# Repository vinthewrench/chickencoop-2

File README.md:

# Chicken Coop Controller

**Firmware and host-side tooling for an offline, solar-aware chicken coop controller based on the ATmega32U4.**

This repository contains:
- A **desktop host build** for testing and development
- An **AVR firmware build** for deployment
- A shared `src/` tree with no generated artifacts

The build system is intentionally explicit and boring:
- C++ only
- No generated files in `src/`
- All object files live under `build/`
- Host and firmware builds are independent

Hardware for this repository is frozen at **Chicken Coop Controller V3.0**.
Firmware and host code must conform to the shipped hardware.

---

## Repository Layout

```
├── Makefile
│   # Top-level build orchestrator
│   # Invokes host/ and firmware/ builds
│
├── README.md
│   # Project overview and build instructions
│
├── coop.cfg
│   # Example/default runtime configuration for host testing
│
├── firmware/
│   # AVR firmware for Chicken Coop Controller V3.0 (avr-g++)
│   ├── Makefile
│   │   # Firmware build rules
│   ├── main_firmware.cpp
│   │   # Firmware entry point (CONFIG + RUN)
│   │   # Shares scheduler/reducer/apply logic with host
│   └── platform/
│       # Board-specific AVR implementation (Hardware V3.0)
│       ├── config_eeprom.cpp
│       │   # Persistent configuration storage (EEPROM)
│       ├── config_sw_avr.cpp
│       │   # Hardware CONFIG switch handling
│       ├── console_io_avr.cpp
│       │   # AVR-side console I/O glue
│       ├── door_avr.cpp
│       │   # Door motor control (real hardware)
│       ├── door_led_avr.cpp
│       │   # Door LED driver (real hardware)
│       ├── door_lock_avr.cpp
│       │   # Lock actuator control (real hardware)
│       ├── relays_avr.cpp
│       │   # Relay pulse drivers (real hardware)
│       ├── rtc.cpp
│       │   # RTC implementation for PCF8523 (I2C)
│       ├── system_sleep_avr.cpp
│       │   # Low-power sleep implementation (AVR)
│       ├── uart.cpp
│       │   # UART service (console/debug)
│       ├── uart.h
│       ├── uptime.cpp
│       │   # System uptime service (AVR)
│       ├── i2c_avr.cpp
│       │   # I2C implementation (RTC, peripherals)
│       └── i2c.h
│
├── host/
│   # Desktop host build and test console (clang++)
│   ├── Makefile
│   ├── main_host.cpp
│   │   # Host entry point (interactive console + scheduler loop)
│   └── platform/
│       # Host-side implementations (no real hardware)
│       ├── config_host.cpp
│       ├── config_sw_host.cpp
│       ├── console_io_host.cpp
│       ├── door_hw_host.cpp
│       ├── door_led_host.cpp
│       ├── lock_hw_host.cpp
│       ├── relays_host.cpp
│       ├── rtc_host.cpp
│       ├── system_sleep_host.cpp
│       └── uptime_host.cpp
│
└── src/
    # Shared, platform-independent logic
    # No main(), no generated files, minimal platform assumptions
    ├── config.h
    ├── config_common.cpp
    ├── config_events.cpp
    ├── config_events.h
    ├── config_sw.h
    │
    ├── events.h
    ├── resolve_when.cpp
    ├── resolve_when.h
    ├── next_event.cpp
    ├── next_event.h
    │
    ├── rtc.h
    ├── rtc_common.cpp
    │
    ├── solar.cpp
    ├── solar.h
    │
    ├── time_dst.cpp
    ├── time_dst.h
    │
    ├── uptime.h
    │
    ├── scheduler.cpp
    ├── scheduler.h
    ├── state_reducer.cpp
    ├── state_reducer.h
    ├── schedule_apply.cpp
    ├── schedule_apply.h
    │
    ├── system_sleep.h
    │
    ├── door_hw.h
    ├── door_led.h
    ├── lock_hw.h
    ├── relay_hw.h
    │
    ├── console/
    │   # Shared console implementation
    │   ├── console.cpp
    │   ├── console.h
    │   ├── console_cmds.cpp
    │   ├── console_time.cpp
    │   ├── console_time.h
    │   ├── console_io.h
    │   ├── mini_printf.cpp
    │   └── mini_printf.h
    │
    └── devices/
        # Abstract device model layer + state machines
        ├── device.h
        ├── device_ids.h
        ├── devices.cpp
        ├── devices.h
        ├── door_device.cpp
        ├── door_state_machine.cpp
        ├── door_state_machine.h
        ├── lock_device.cpp
        ├── lock_state_machine.cpp
        ├── lock_state_machine.h
        ├── relay_device.cpp
        ├── led_device.cpp
        ├── led_state_machine.cpp
        ├── led_state_machine.h
        └── foo_device.cpp
```

### Rules
- `src/` must always remain clean
- No `.o`, `.elf`, `.hex`, or generated files under `src/`
- All build products live under `build/`
- Host and firmware builds do **not** share object files

---

## Top-Level Make Targets

Run all commands from the **repository root**.

```sh
make
make all
```
Builds **both** host and firmware (default).

```sh
make host
```
Builds **host console only**.

```sh
make firmware
```
Builds **AVR firmware only**.

```sh
make clean
```
Cleans host and firmware build outputs.

---

## Host Console (Desktop Test Environment)

### Purpose
The host build is a functional test harness for:
- Command parsing
- Solar and schedule calculations
- Configuration handling
- Console behavior
- Simulated RTC, EEPROM, relays, door, lock, and uptime

### Build
```sh
cd host
make
```

### Run
```sh
./build/console_host
```

### Exit
```
exit
```

The host build uses **clang++** and builds entirely under `host/build/`.

No source files live under `host/src/`. All shared logic comes from the top-level `src/` directory.

---

## Firmware (ATmega32U4)

### Build
```sh
cd firmware
make
```

### Outputs
```
coop_firmware.elf
coop_firmware.hex
coop_firmware.map
```

### Toolchain
- `avr-g++`
- Target MCU: **ATmega32U4**
- Clock: **Internal 8 MHz RC oscillator**

---

## Flashing (Atmel-ICE, ISP)

```sh
cd firmware
make flash
```

Assumptions:
- Atmel-ICE
- ISP mode
- USB transport
- No bootloader

---

## Fuse Management (LOCKED VALUES)

⚠️ **WARNING**  
Fuse settings are hardware configuration. Treat as write-once per board.

### Read fuses
```sh
cd firmware
make check-fuses
```

### Program fuses (ONLY on new or recovered chips)
```sh
cd firmware
make set-fuses
```

### Locked Fuse Values

| Fuse | Value | Meaning |
|-----:|:-----:|--------|
| Low  | 0xFF  | Internal 8 MHz RC, CLKDIV8 disabled |
| High | 0xD8  | JTAG disabled, reset enabled |
| Ext  | 0xF5  | Brown-out detect ≈ 4.3 V |

These values are fixed by the hardware design and should not be changed casually.

---

## Time, Solar, and DST Behavior

- RTC runs in **local civil time**
- `tz` is the **standard time offset** (e.g. `-6` for Central)
- Daylight Saving Time is handled via **US rules (post-2007)**
- DST logic lives in `src/time_dst.cpp`
- DST is applied at the **solar computation boundary**, not inside the solar math itself

This system is fully offline and deterministic.

---

## Version Injection

### Single source of truth
Defined in the **top-level Makefile**:

Note: `PROJECT_VERSION` refers to the **firmware/software version**, not the hardware revision.
Hardware for this repository is **Chicken Coop Controller V3.0**.

```make
PROJECT_VERSION := 2.6.x
```

### Injected into builds as
```c++
PROJECT_VERSION
```

### Used for
- Startup banner
- `version` console command
- Debug output

---

## Sanity Check Workflow

From the repo root:

```sh
make clean
make
make host
make firmware
```

If this completes without errors, the build system is stable.

---

## Final Notes

- GNU Make **3.81 compatible**
- Relative paths used intentionally
- No clever build magic
- If something breaks, it’s real code, not glue

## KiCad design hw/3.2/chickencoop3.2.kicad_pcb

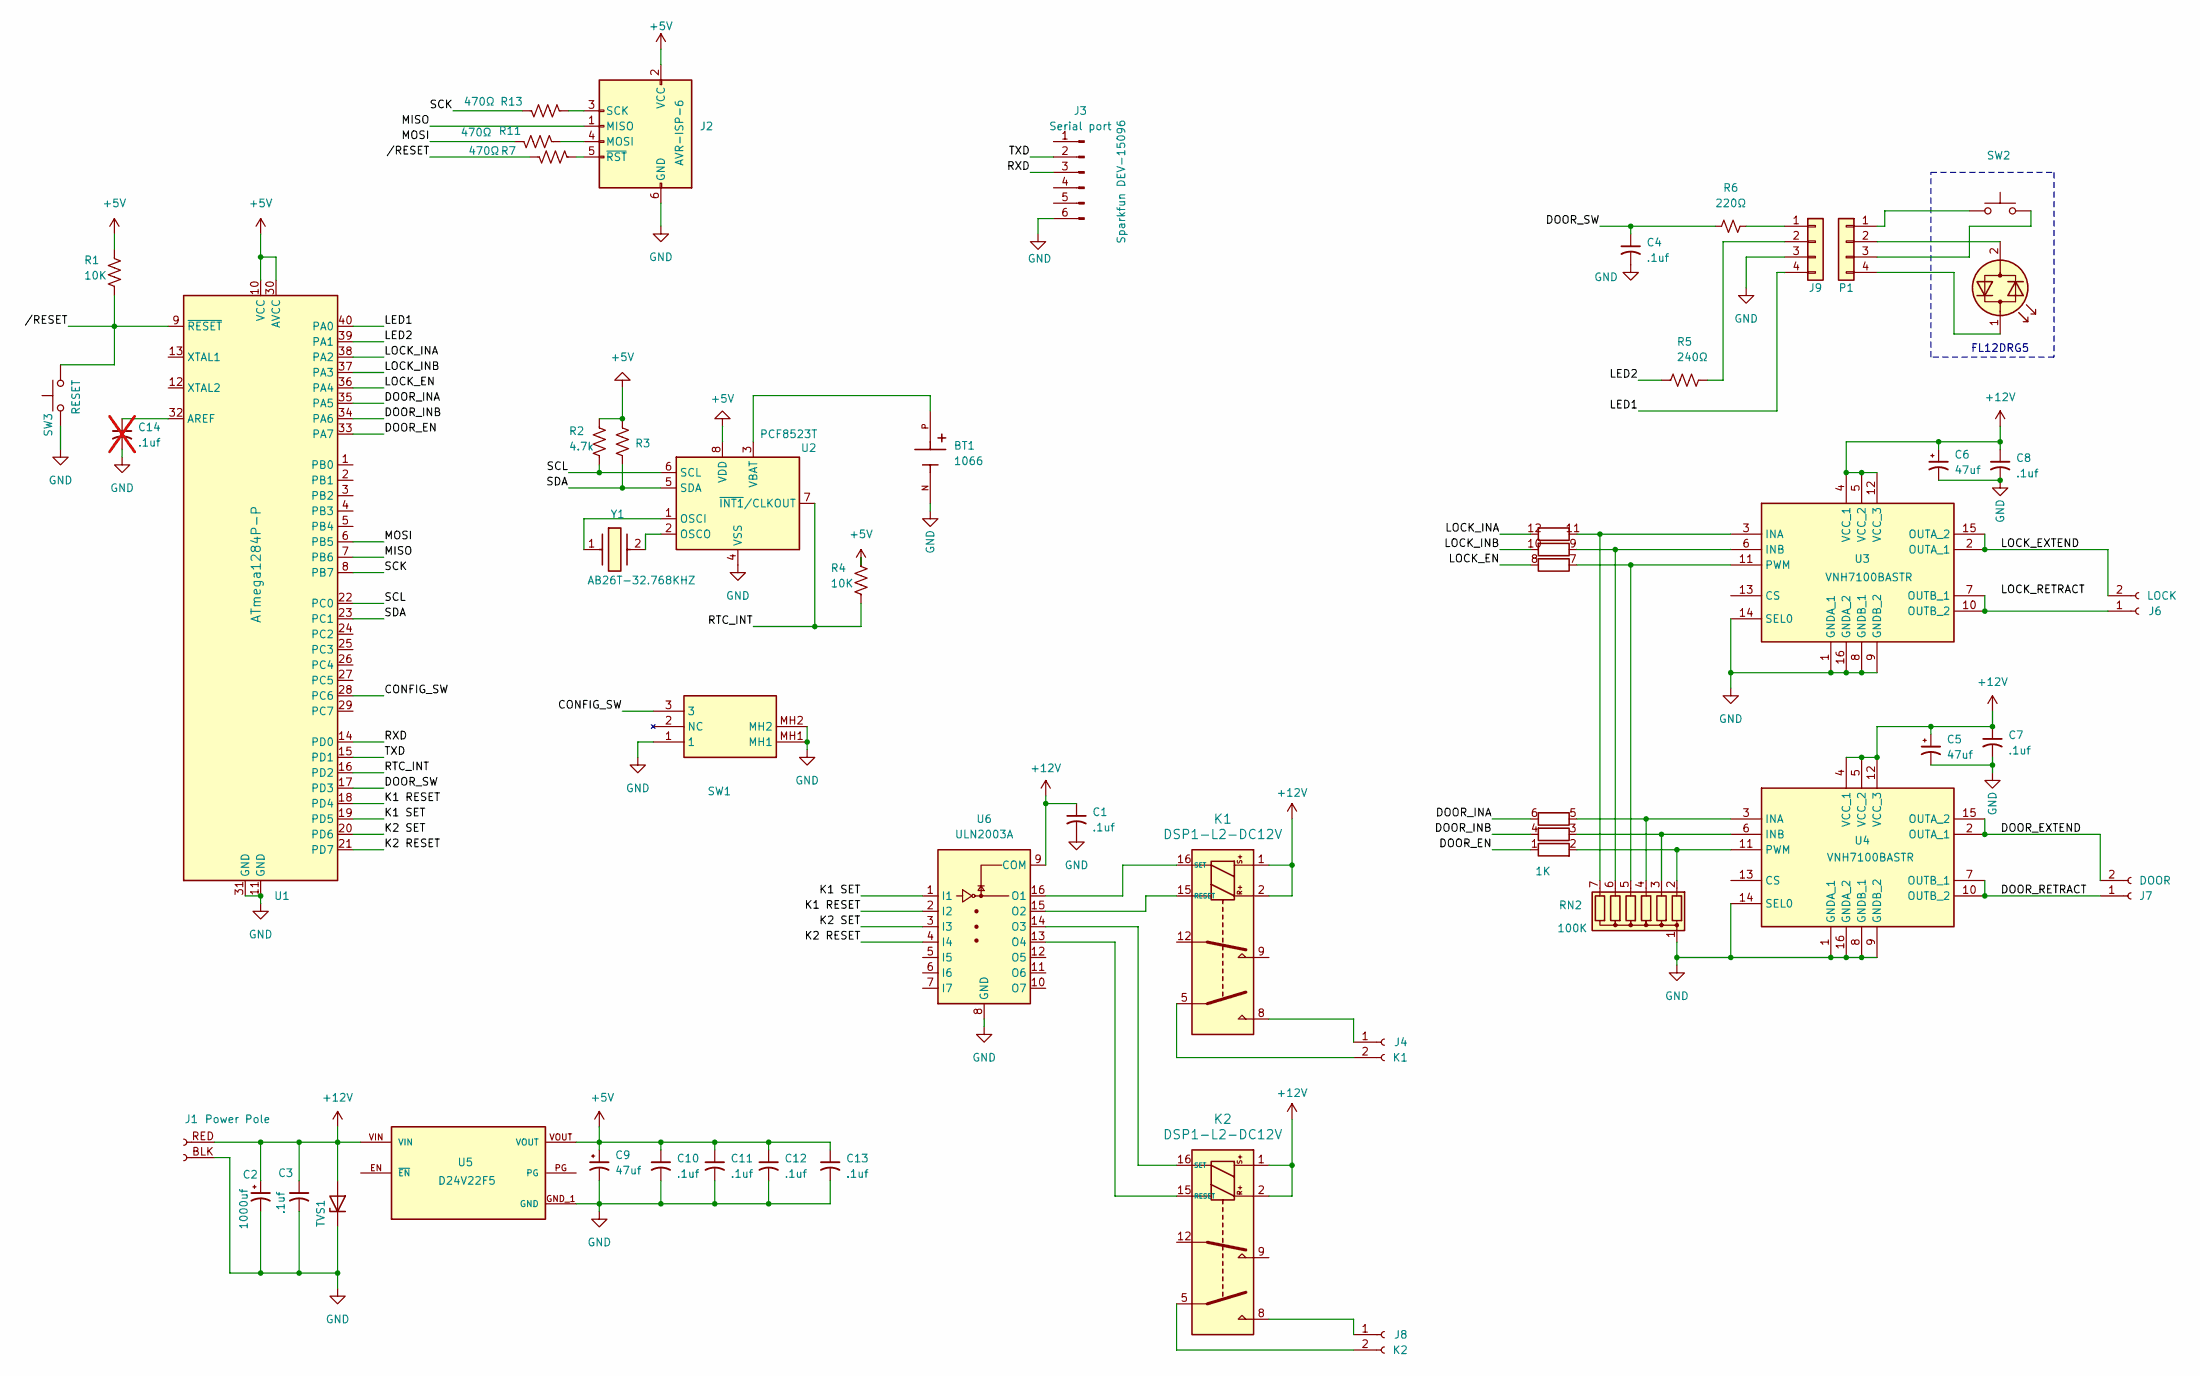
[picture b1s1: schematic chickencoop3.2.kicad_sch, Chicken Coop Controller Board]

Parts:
BT1: 1066; BAT_1066; PARTREV E
C1, C3, C4, C7, C8, C10, C11, C12, C13: .1uf; RCER71H104K0DBH03A
C2: 1000uf; CP_Radial_D10.0mm_P5.00mm
C5, C6, C9: 47uf; CP_Radial_D5.0mm_P2.00mm
C14: .1uf; RCER71H104K0DBH03A; not fitted
D1: LED_Dual_Bidirectional
J1: Power Pole; powerpole
J2: AVR-ISP-6; PinHeader_2x03_P2.54mm_Vertical
J3: Serial port; PinHeader_1x06_P2.54mm_Vertical
J4: K1; TerminalBlock_Phoenix_MKDS-1,5-2-5.08_1x02_P5.08mm_Horizont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
J6: LOCK; TerminalBlock_Phoenix_MKDS-1,5-2-5.08_1x02_P5.08mm_Horizont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
J7: DOOR; TerminalBlock_Phoenix_MKDS-1,5-2-5.08_1x02_P5.08mm_Horizont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
J8: K2; TerminalBlock_Phoenix_MKDS-1,5-2-5.08_1x02_P5.08mm_Horizont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
J9: Mini‑Fit Jr; Molex_Mini-Fit_Jr_5566-04A_2x02_P4.20mm_Vertical
K1, K2: DSP1-L2-DC12V
P1: Mini‑Fit Jr; Molex_Mini-Fit_Jr_5566-04A_2x02_P4.20mm_Vertical
R1, R4: 10K; R_Axial_DIN0204_L3.6mm_D1.6mm_P7.62mm_Horizontal
R2: 4.7k; R_Axial_DIN0204_L3.6mm_D1.6mm_P7.62mm_Horizontal
R3: 4.7K; R_Axial_DIN0204_L3.6mm_D1.6mm_P7.62mm_Horizontal
R5: 240Ω; R_Axial_DIN0204_L3.6mm_D1.6mm_P7.62mm_Horizontal
R6: 220Ω; R_Axial_DIN0204_L3.6mm_D1.6mm_P7.62mm_Horizontal
R7, R11, R13: 470Ω; R_Axial_DIN0204_L3.6mm_D1.6mm_P7.62mm_Horizontal
RN2: 100K; R_Array_SIP7; Manufacturer_Part_Number 4607X-101-104LF
RN4: 1K; R_Array_SIP12; Manufacturer_Part_Number 4612X-102-102LF
SW1: SW_SPST; AS11CH; Mouser Part Number 633-AS11CH
SW2: SW_Push
SW3: RESET; SW_PUSH_6mm
TVS1: P6SMB18A; D_SMB_Handsoldering
U1: ATmega1284P-P; DIP-40_W15.24mm
U2: PCF8523T; SOIC-8_3.9x4.9mm_P1.27mm
U3, U4: VNH7100BASTR; SOIC127P600X175-16N; Manufacturer_Part_Number VNH7100BASTR; Mouser Part Number 511-VNH7100BASTR
U5: D24V22F5; MODULE_5V_2.5A_STEP-DOWN_D24V22F5; PARTREV 12 November 2015
U6: ULN2003A; DIP-16_W7.62mm
Y1: AB26T-32.768KHZ; AB26T32768KHZ; Mouser Part Number 815-AB26T-32.768KHZ

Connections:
+5V: C9.1, C10.1, C11.1, C12.1, C13.1, J2.2 (VCC), R1.1, R2.1, R3.1, R4.1, U1.10 (VCC), U1.30 (AVCC), U2.8 (VDD), U5.VOUT
+12V: C1.1, C2.1, C3.1, C5.1, C6.1, C7.1, C8.1, J1.RED, K1.1, K1.2, K2.1, K2.2, TVS1.2 (A), U3.4 (VCC_1), U3.5 (VCC_2), U3.12 (VCC_3), U4.4 (VCC_1), U4.5 (VCC_2), U4.12 (VCC_3), U5.VIN, U6.9 (COM)
/CONFIG_SW: SW1.3, U1.28 (PC6)
/DOOR_EN: RN4.1 (R1.1), U1.33 (PA7)
/DOOR_EXTEND: J7.2, U4.2 (OUTA_1), U4.15 (OUTA_2)
/DOOR_INA: RN4.6 (R3.2), U1.35 (PA5)
/DOOR_INB: RN4.4 (R2.2), U1.34 (PA6)
/DOOR_RETRACT: J7.1, U4.7 (OUTB_1), U4.10 (OUTB_2)
/DOOR_SW: C4.1, R6.1, U1.17 (PD3)
/K1 RESET: U1.18 (PD4), U6.2 (I2)
/K1 SET: U1.19 (PD5), U6.1 (I1)
/K2 RESET: U1.21 (PD7), U6.4 (I4)
/K2 SET: U1.20 (PD6), U6.3 (I3)
/LED1: J9.4, U1.40 (PA0)
/LED2: R5.1, U1.39 (PA1)
/LOCK_EN: RN4.8 (R4.2), U1.36 (PA4)
/LOCK_EXTEND: J6.2, U3.2 (OUTA_1), U3.15 (OUTA_2)
/LOCK_INA: RN4.12 (R6.2), U1.38 (PA2)
/LOCK_INB: RN4.10 (R5.2), U1.37 (PA3)
/MISO: J2.1 (MISO), U1.7 (PB6)
/MOSI: R11.1, U1.6 (PB5)
/RTC_INT: R4.2, U1.16 (PD2), U2.7 (~INT1/CLKOUT)
/RXD: J3.3, U1.14 (PD0)
/SCK: R13.1, U1.8 (PB7)
/SCL: R2.2, U1.22 (PC0), U2.6 (SCL)
/SDA: R3.2, U1.23 (PC1), U2.5 (SDA)
/TXD: J3.2, U1.15 (PD1)
//RESET: R1.2, R7.1, SW3.2, U1.9 (~RESET)
GND: BT1.N, C1.2, C2.2, C3.2, C4.2, C5.2, C6.2, C7.2, C8.2, C9.2, C10.2, C11.2, C12.2, C13.2, C14.2, J1.BLK, J2.6 (GND), J3.6, J9.3, RN2.1 (common), SW1.1, SW1.MH1, SW1.MH2, SW3.1, TVS1.1 (K), U1.11 (GND), U1.31 (GND), U2.4 (VSS), U3.1 (GNDA_1), U3.8 (GNDB_1), U3.9 (GNDB_2), U3.14 (SEL0), U3.16 (GNDA_2), U4.1 (GNDA_1), U4.8 (GNDB_1), U4.9 (GNDB_2), U4.14 (SEL0), U4.16 (GNDA_2), U5.GND_1 (GND), U5.GND_2 (GND), U6.8 (GND)
unnamed: D1.1 (KA), P1.4
unnamed: D1.2 (AK), P1.2
unnamed: J2.4 (MOSI), R11.2
unnamed: J2.3 (SCK), R13.2
unnamed: J2.5 (~RST), R7.2
unnamed: J4.1, K1.8
unnamed: J4.2, K1.5
unnamed: J6.1, U3.7 (OUTB_1), U3.10 (OUTB_2)
unnamed: J8.1, K2.8
unnamed: J8.2, K2.5
unnamed: J9.1, R6.2
unnamed: J9.2, R5.2
unnamed: K1.15 (RESET), U6.15 (O2)
unnamed: K1.16 (SET), U6.16 (O1)
unnamed: K2.15 (RESET), U6.13 (O4)
unnamed: K2.16 (SET), U6.14 (O3)
unnamed: P1.1, SW2.1
unnamed: P1.3, SW2.2
unnamed: RN2.2 (R1), RN4.2 (R1.2), U4.11 (PWM)
unnamed: RN2.3 (R2), RN4.3 (R2.1), U4.6 (INB)
unnamed: RN2.4 (R3), RN4.5 (R3.1), U4.3 (INA)
unnamed: RN2.5 (R4), RN4.7 (R4.1), U3.11 (PWM)
unnamed: RN2.6 (R5), RN4.9 (R5.1), U3.6 (INB)
unnamed: RN2.7 (R6), RN4.11 (R6.1), U3.3 (INA)
unnamed: C14.1, U1.32 (AREF)
unnamed: U2.1 (OSCI), Y1.1
unnamed: U2.2 (OSCO), Y1.2
unnamed: BT1.P, U2.3 (VBAT)

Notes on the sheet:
FL12DRG5

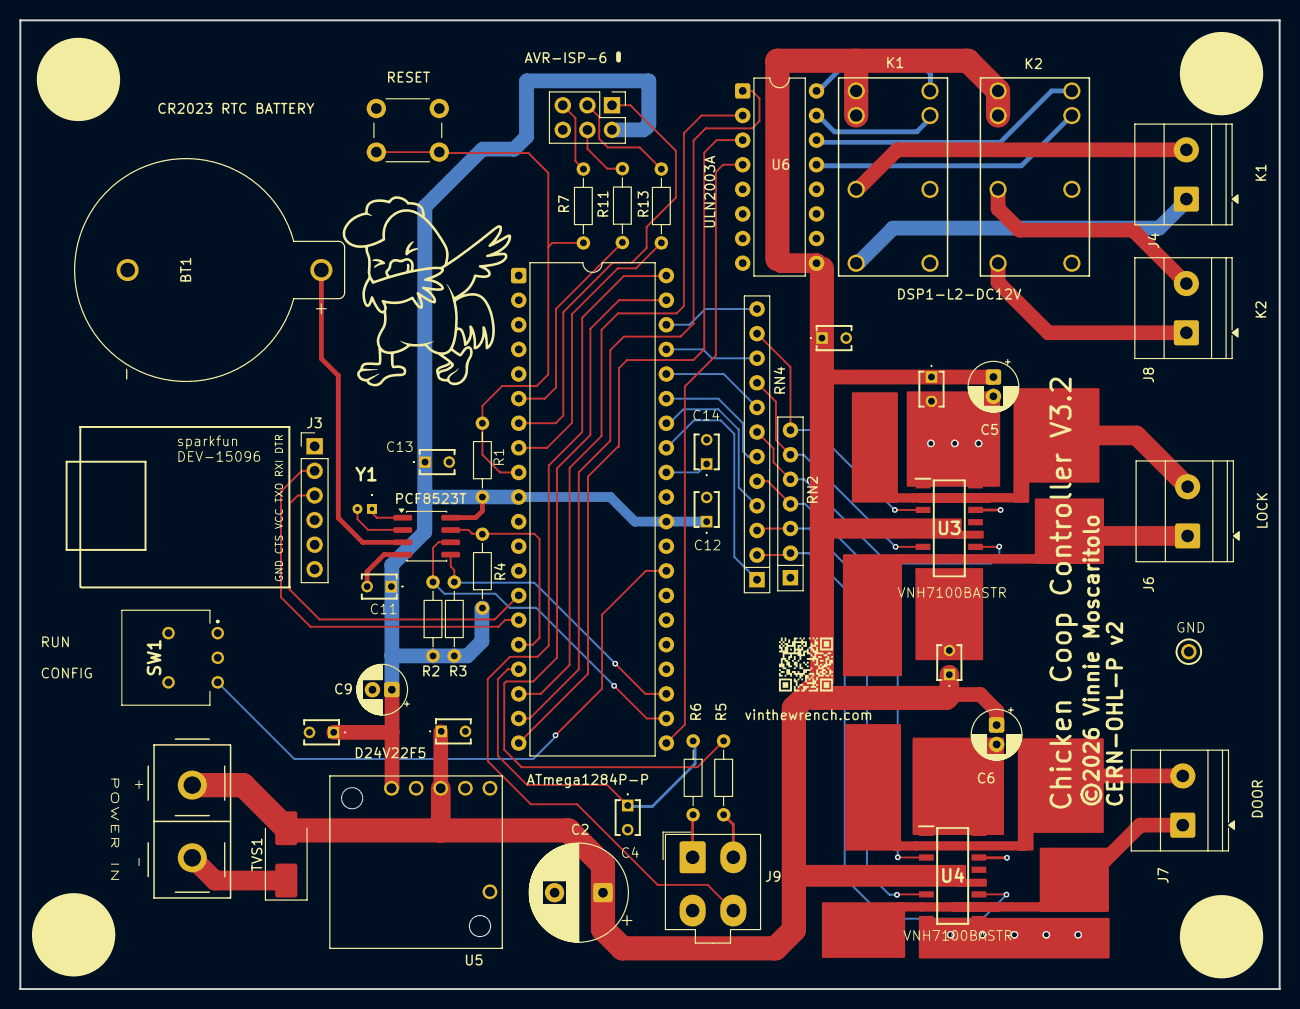
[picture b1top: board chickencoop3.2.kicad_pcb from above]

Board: 2 copper layers, 130.0 x 100.0 mm, 47 parts (0 on the bottom side), 53 nets.

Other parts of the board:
TP3: GND; 5000

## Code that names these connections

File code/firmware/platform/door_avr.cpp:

/*
 * door_avr.cpp
 *
 * Project: Chicken Coop Controller
 * Purpose: Door actuator hardware control (AVR) using VNH7100BASTR
 *
 * Notes:
 *  - Pure hardware driver
 *  - Direction via INA / INB
 *  - Power gated via EN (used as digital enable, no PWM)
 *  - No timing, no state, no policy
 *  - Masked PORTF writes only
 *
 * Updated: 2026-01-05
 */

#include "door_hw.h"

#include <avr/io.h>
#include <stdint.h>

/* --------------------------------------------------------------------------
 * Pin mapping (LOCKED to board schematic)
 * -------------------------------------------------------------------------- */
/* DOOR_INA -> PF5 (pin 38) */
/* DOOR_INB -> PF6 (pin 37) */
/* DOOR_EN  -> PF7 (pin 36) */

#define DOOR_INA_BIT   (1u << PF5)
#define DOOR_INB_BIT   (1u << PF6)
#define DOOR_EN_BIT    (1u << PF7)

/* --------------------------------------------------------------------------
 * Internal helpers (masked writes only)
 * -------------------------------------------------------------------------- */

static inline void set_bits(uint8_t mask)
{
    PORTF |= mask;
}

static inline void clear_bits(uint8_t mask)
{
    PORTF &= (uint8_t)~mask;
}

/* --------------------------------------------------------------------------
 * One-time hardware init guard
 * -------------------------------------------------------------------------- */

static inline void door_hw_init_once(void)
{
    static uint8_t init = 0;
    if (init)
        return;

    /* Configure control pins as outputs */
    DDRF |= (DOOR_INA_BIT | DOOR_INB_BIT | DOOR_EN_BIT);

    /* Safe default:
     *  - EN = 0  (motor off)
     *  - INA = 0
     *  - INB = 0
     */
    clear_bits(DOOR_EN_BIT | DOOR_INA_BIT | DOOR_INB_BIT);

    init = 1;
}

/* --------------------------------------------------------------------------
 * Public API
 * -------------------------------------------------------------------------- */

void door_hw_set_open_dir(void)
{
    door_hw_init_once();

    /* INA=1, INB=0 */
    clear_bits(DOOR_INB_BIT);
    set_bits(DOOR_INA_BIT);
}

void door_hw_set_close_dir(void)
{
    door_hw_init_once();

    /* INA=0, INB=1 */
    clear_bits(DOOR_INA_BIT);
    set_bits(DOOR_INB_BIT);
}

void door_hw_enable(void)
{
    door_hw_init_once();
    set_bits(DOOR_EN_BIT);
}

void door_hw_disable(void)
{
    door_hw_init_once();
    clear_bits(DOOR_EN_BIT);
}

void door_hw_stop(void)
{
    door_hw_init_once();

    /* Disable power first, then neutralize direction */
    clear_bits(DOOR_EN_BIT);
    clear_bits(DOOR_INA_BIT | DOOR_INB_BIT);
}

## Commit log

2025-12-29 Initial import: coop firmware + host skeleton
    - Add AVR firmware target for ATmega32U4 @ 8 MHz
    - Add host build for logic testing without hardware
    - Core modules: RTC, solar, console, door, lock, config
    - Shared src/ tree with platform-specific implementations
    - Deterministic, offline control model (no network, no cloud)
    - Add strict .gitignore to exclude macOS junk and build artifacts
2025-12-31 sort event list by time
2025-12-31 added next event
2025-12-31 more cleanup and makefile hacks
2026-01-05 corrected some pinouts
2026-01-05 check in hardware
2026-01-05 ZED noise removal
2026-01-05 updates for door and lock
2026-01-06 clean up console input async
2026-01-06 state machine for door
2026-01-08 bunch of work on scheduling and events
2026-01-08 Scheduler refactor: unify host/firmware execution, add ETag, fix time sampling, enable RTC sleep
    Host and firmware now run identical scheduler logic.
    Schedule reevaluates on minute tick or config/event changes.
    Firmware sleeps via RTC alarm between events.
2026-01-08 readme directory update
2026-01-17 firmware is working in console -
2026-01-18 Remove obsolete files
2026-01-20 version 3.2 HW - using ATmega1284P now
2026-02-02 more updates
2026-02-04 moved HW
2026-02-04 Checkpoint: working LED pulse, RTC, scheduler, and door control (lock unsafe)
2026-02-07 rtc: disable PCF8523 CLKOUT and stabilize INT behavior
    - Explicitly set COF=111 in REG 0x0F during rtc_init()
    - Prevent unintended 32.768 kHz square wave on INT/CLKOUT
    - Confirm I2C register writes and readbacks
    - Establish clean baseline for deterministic alarm + sleep debugging
    Shop session validation:
    - Verified CLKOUT disable on scope
2026-02-07 forgot to restore uptime_init this is critical for device timing
2026-02-07 AI gave me bad set time code -- revert to what I know
2026-02-11 improving main loop
2026-02-12 still messing with RTC issues
2026-02-12 door and schedule actions are better
2026-02-13 directory cleanup now that we do firmware builds only
2026-02-14 more rtc, scheduler and cmd fixes

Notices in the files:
hw/3.2/chickencoop3.2.kicad_pcb:
©2026 Vinnie Moscaritolo
CERN-OHL-P v2
hw/3.2/chickencoop3.2.kicad_sch:
CERN-OHL-P v2 Permissive Open Hardware Licence
